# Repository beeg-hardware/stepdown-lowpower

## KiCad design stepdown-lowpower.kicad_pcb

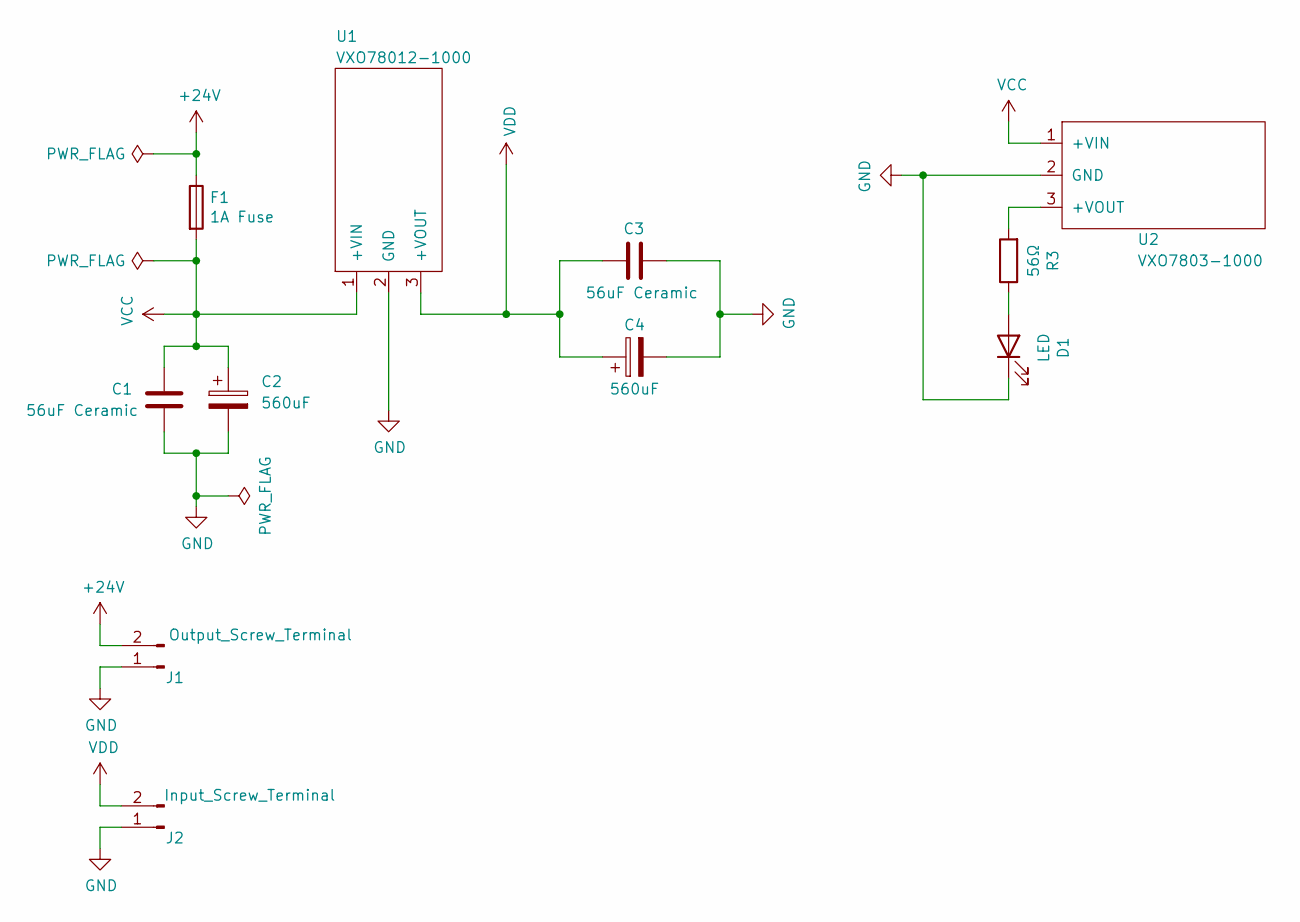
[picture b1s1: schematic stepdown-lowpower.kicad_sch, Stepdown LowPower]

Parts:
C1, C3: 56uF Ceramic; C_Rect_L7.0mm_W3.5mm_P5.00mm
C2, C4: 560uF; CP_Radial_D18.0mm_P7.50mm
D1: LED; LED_Rectangular_W3.0mm_H2.0mm
F1: 1A Fuse; Fuseholder_Cylinder-5x20mm_Littlelfuse_520_Horizontal_Open
J1: Output_Screw_Terminal; PhoenixContact_MSTBA_2,5_2-G-5,08_1x02_P5.08mm_Horizontal
J2: Input_Screw_Terminal; PhoenixContact_MSTBA_2,5_2-G-5,08_1x02_P5.08mm_Horizontal
R3: 56Ω; R_Axial_DIN0207_L6.3mm_D2.5mm_P10.16mm_Horizontal
U1: VXO78012-1000; VXO78-1000
U2: VXO7803-1000; VXO78-1000

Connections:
+24V: F1.1, J1.2
GND: C1.2, C2.2, C3.2, C4.2, D1.1 (K), J1.1, J2.1, U1.2 (GND), U2.2 (GND)
unnamed: D1.2 (A), R3.1
unnamed: R3.2, U2.3 (+VOUT)
VCC: C1.1, C2.1, F1.2, U1.1 (+VIN), U2.1 (+VIN)
VDD: C3.1, C4.1, J2.2, U1.3 (+VOUT)

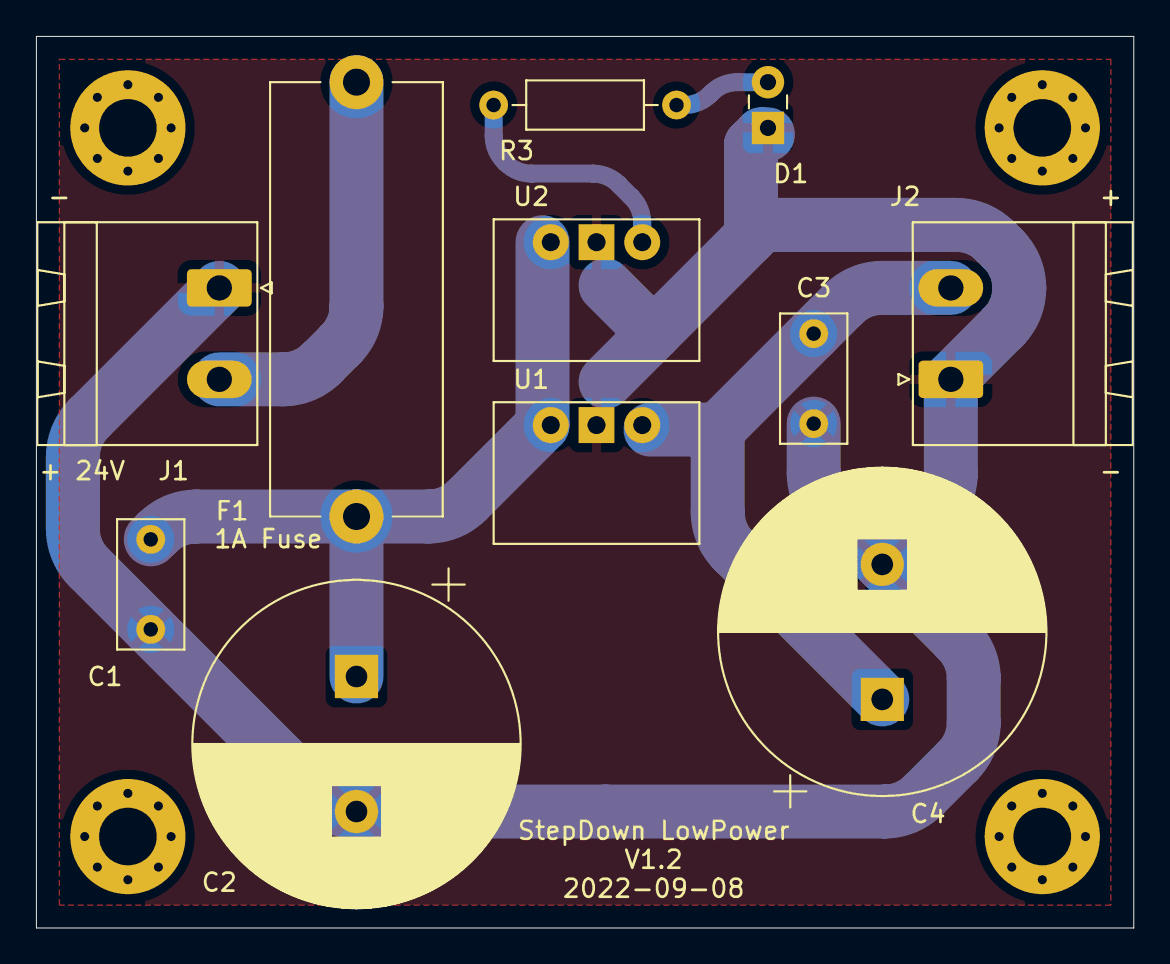
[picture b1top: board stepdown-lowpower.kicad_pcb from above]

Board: 2 copper layers, 61.0 x 49.5 mm, 15 parts (0 on the bottom side), 6 nets.

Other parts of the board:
H1, H2, H3, H4: MountingHole_3.2mm_M3_Pad_Via

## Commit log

2022-09-08 Import from older project
2022-09-26 License and footprint updated
2022-09-27 Silkscreen update
